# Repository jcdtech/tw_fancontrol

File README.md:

# TW Fan Control
Two/Three-Wire Fan Controller

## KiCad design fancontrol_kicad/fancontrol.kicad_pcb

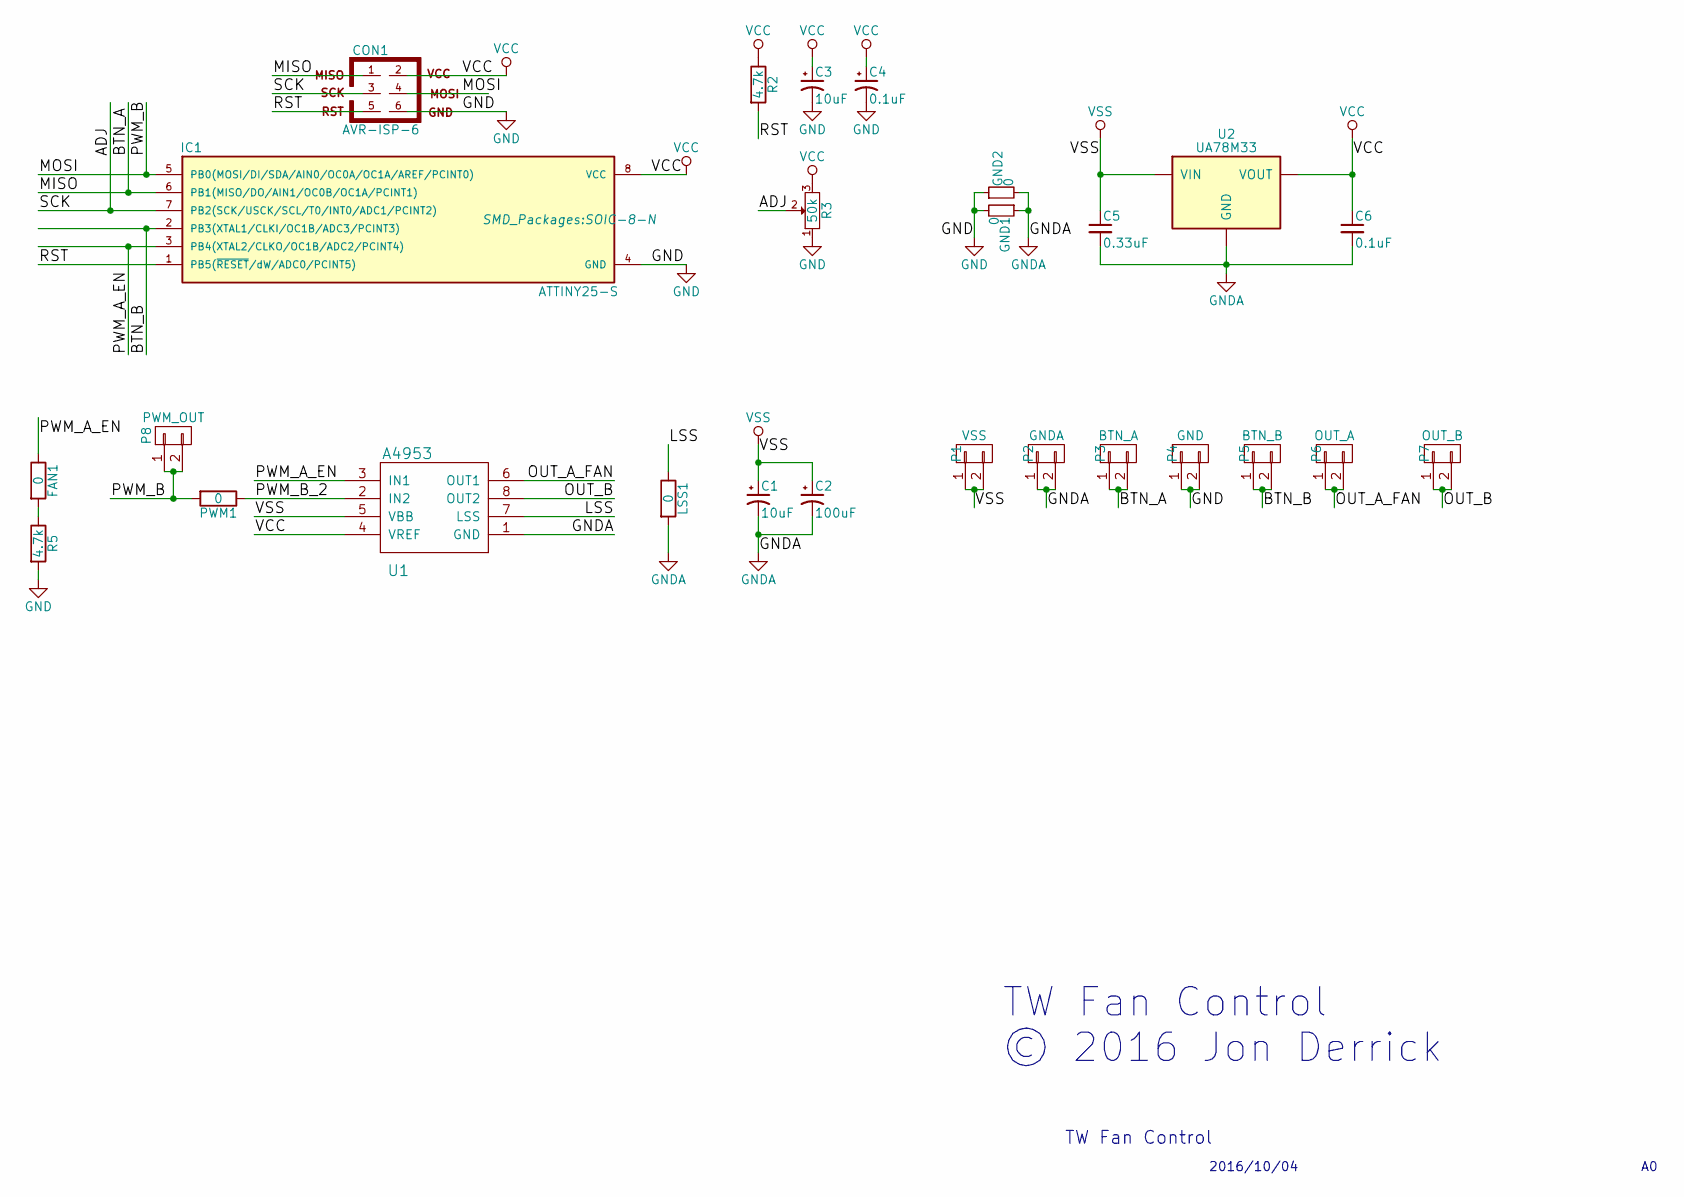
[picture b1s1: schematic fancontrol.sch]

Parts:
C1, C3: 10uF; TantalC_SizeA_EIA-3216_HandSoldering
C2: 100uF; c_elec_6.3x5.8
C4, C6: 0.1uF; C_0805_HandSoldering
C5: 0.33uF; C_0805_HandSoldering
CON1: AVR-ISP-6; Pin_Header_Straight_2x03
FAN1: 0; GS2
GND1, GND2: 0; GS2
IC1: ATTINY25-S; SOIC-8-N
LSS1: 0; R_0603_HandSoldering
P1: VSS; RIGHT_TERM
P2: GNDA; RIGHT_TERM
P3: BTN_A; RIGHT_TERM
P4: GND; RIGHT_TERM
P5: BTN_B; RIGHT_TERM
P6: OUT_A; RIGHT_TERM
P7: OUT_B; RIGHT_TERM
P8: PWM_OUT; RIGHT_TERM
PWM1: 0; GS2
R2, R5: 4.7k; R_0805_HandSoldering
R3: 50k; POT_SMD
U1: A4953; SOIC-8-N-PAD
U2: UA78M33; SOT-223

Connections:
/ADJ: CON1.3, IC1.7 (PB2(SCK/USCK/SCL/T0/INT0/ADC1/PCINT2)), R3.2
/BTN_A: CON1.1, IC1.6 (PB1(MISO/DO/AIN1/OC0B/OC1A/PCINT1)), P3.1, P3.2
/BTN_B: IC1.2 (PB3(XTAL1/CLKI/OC1B/ADC3/PCINT3)), P5.1, P5.2
/LSS: LSS1.1, U1.7 (LSS)
/MOSI: CON1.4, IC1.5 (PB0(MOSI/DI/SDA/AIN0/OC0A/OC1A/AREF/PCI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), P8.1, P8.2, PWM1.2
/OUT_A_FAN: P6.1, P6.2, U1.6 (OUT1)
/OUT_B: P7.1, P7.2, U1.8 (OUT2)
/PWM_A_EN: FAN1.1, IC1.3 (PB4(XTAL2/CLKO/OC1B/ADC2/PCINT4)), U1.3 (IN1)
/PWM_B_2: PWM1.1, U1.2 (IN2)
/RST: CON1.5, IC1.1 (PB5(~RESET~/dW/ADC0/PCINT5)), R2.2
GND: C3.2, C4.2, CON1.6, GND1.2, GND2.1, IC1.4 (GND), P4.1, P4.2, R3.1, R5.2
GNDA: C1.2, C2.2, C5.2, C6.2, GND1.1, GND2.2, LSS1.2, P2.1, P2.2, U1.1 (GND), U2.2 (GND), U2.4 (GND)
unnamed: FAN1.2, R5.1
VCC: C3.1, C4.1, C6.1, CON1.2, IC1.8 (VCC), R2.1, R3.3, U1.4 (VREF), U2.3 (VOUT)
VSS: C1.1, C2.1, C5.1, P1.1, P1.2, U1.5 (VBB), U2.1 (VIN)

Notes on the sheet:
TW Fan Control
2016/10/04
TW Fan Control © 2016 Jon Derrick

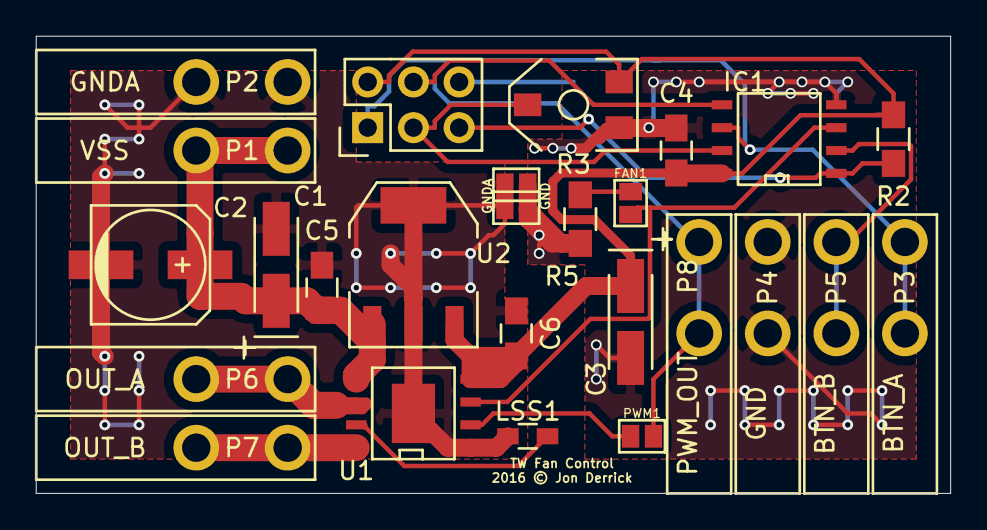
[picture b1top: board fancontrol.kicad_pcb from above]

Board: 2 copper layers, 50.8 x 25.4 mm, 26 parts (0 on the bottom side), 15 nets.

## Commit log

2016-10-13 First commit.
    Tested on breadboard with active-low LED.
2016-10-13 General cleanup.
    Added individual PWM active high knobs and several comments.
    Staged ADC factor code.
2016-10-13 Update Makefile for attiny25 and rename source code file.
2016-10-13 Fixed up header
2016-10-13 Added ADC initialization and polling code.
    Untested
2016-10-13 Corrected for new pinout using FWD:Counter 1, REV:Counter 0
    Added stubs and comments for MODE selection
2016-10-13 First Schematic and PCB Commit
    v1 design
2016-10-13 Added functionality for two/three wire modes
    Detecting the mode is next!
2016-10-13 Added mode detection functionality
    Untested
2016-10-23 First prototype
    Fixed several wrong assumptions about sleep mode.
    Fixed a few other logic bugs and incorrect register assignments.
    Changed MODE adc thresh to 1/2 VCC. With 4.7K to ground and a 10k
    pullup, it should read about 1/3 VCC.
    Tested both Two and Three wire mode with 12V VSS.

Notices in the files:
fancontrol_kicad/fancontrol.kicad_pcb:
2016 © Jon Derrick
